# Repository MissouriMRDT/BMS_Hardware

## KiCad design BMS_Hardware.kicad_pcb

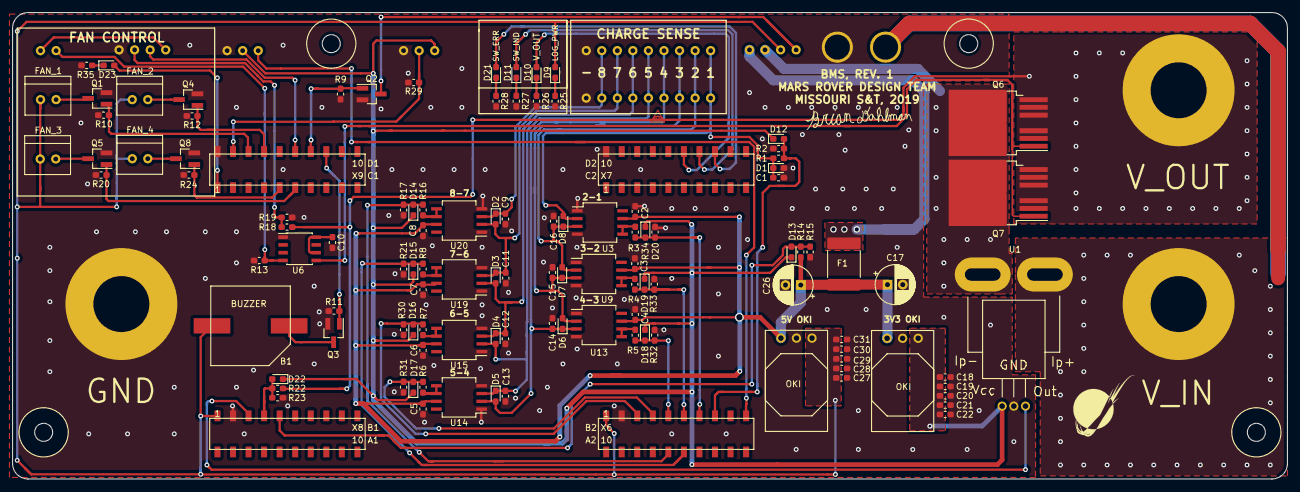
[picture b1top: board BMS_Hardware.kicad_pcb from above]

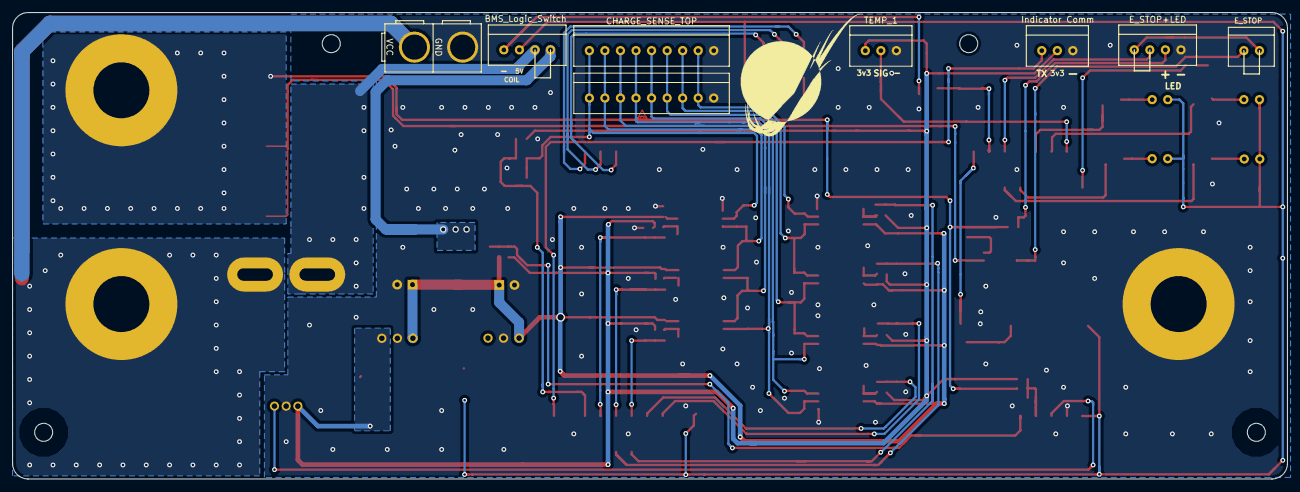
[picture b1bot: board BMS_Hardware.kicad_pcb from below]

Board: 2 copper layers, 208.3 x 76.2 mm, 123 parts (8 on the bottom side), 63 nets.

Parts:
B1: BUZZER_SMI_1324_TW_5V_2_R
C1, C2, C3, C4, C5, C6, C7, C8, C9, C11, C12, C13, C14, C15, C16: 1u; C_0603_1608Metric_Pad1.05x0.95mm_HandSolder
C10, C18, C19, C20, C21, C27, C28, C29, C30: 10u; C_0603_1608Metric_Pad1.05x0.95mm_HandSolder
C17, C26: 22u 50V; CP_Radial_D6.3mm_P2.50mm
C22, C31: 0.1u; C_0603_1608Metric_Pad1.05x0.95mm_HandSolder
Conn1: CHARGE_SENSE_BOTTOM; MOLEX_SL_09_Vertical
Conn2: CHARGE_SENSE_TOP; MOLEX_SL_09_Vertical
Conn3: AndersonPP; Vertical Anderson Double
D1, D2, D3, D4, D5, D6, D7, D8: 7.5V; D_0603_1608Metric_Pad1.05x0.95mm_HandSolder
D9: LOG_PWR_LED; LED_0603_1608Metric_Pad1.05x0.95mm_HandSolder
D10: PACK_V_IND_LED_ORANGE; LED_0603_1608Metric_Pad1.05x0.95mm_HandSolder
D11: SW_IND_LED_BLUE; LED_0603_1608Metric_Pad1.05x0.95mm_HandSolder
D12, D13, D14, D15, D16, D17, D18, D19, D20, D22: D_Schottky; D_0603_1608Metric_Pad1.05x0.95mm_HandSolder
D21: SW_ERR_LED_RED; LED_0603_1608Metric_Pad1.05x0.95mm_HandSolder
D23: FAN_PWR_LED_ORANGE; LED_0603_1608Metric_Pad1.05x0.95mm_HandSolder
F1: PTC2920; Fuse_2920_7451Metric
Q1, Q2, Q3, Q4, Q5, Q8: 2N7002PW; SOT-23_Handsoldering
Q6, Q7: IRLS3034-7P; IRLS3034_TO-263-7_P
R1, R3, R4, R5, R6, R7, R8, R9, R13, R16, R19: 10k; R_0603_1608Metric_Pad1.05x0.95mm_HandSolder
R2, R17, R21, R30, R31, R32, R33, R34: 36.5k; R_0603_1608Metric_Pad1.05x0.95mm_HandSolder
R10, R12, R20, R24: 100K; R_0603_1608Metric_Pad1.05x0.95mm_HandSolder
R11: 10K; R_0603_1608Metric_Pad1.05x0.95mm_HandSolder
R14, R22: 1M; R_0603_1608Metric_Pad1.05x0.95mm_HandSolder
R15, R23: 100k; R_0603_1608Metric_Pad1.05x0.95mm_HandSolder
R18: 4k; R_0603_1608Metric_Pad1.05x0.95mm_HandSolder
R25, R27, R28, R35: 500; R_0603_1608Metric_Pad1.05x0.95mm_HandSolder
R26: 1.5k; R_0603_1608Metric_Pad1.05x0.95mm_HandSolder
R29: 4.7k; R_0603_1608Metric_Pad1.05x0.95mm_HandSolder
U1: ACS759ECB-200B-PFF-T; PFF_Leadform_5pins
U2: FAN_1; MOLEX_SL_02_Vertical
U3, U9, U13, U14, U15, U19, U20: INA132; SO-8_5.3x6.2mm_P1.27mm
U4: FAN_2; MOLEX_SL_02_Vertical
U5: BMS_Logic_Switch; MOLEX_SL_04_Vertical
U6: LT1910; SOIC-8_3.9x4.9mm_Pitch1.27mm
U7: E_STOP; MOLEX_SL_02_Vertical
U8: FAN_3; MOLEX_SL_02_Vertical
U10: E_STOP+LED; MOLEX_SL_04_Vertical
U11: TEMP_1; MOLEX_SL_03_Vertical
U12: FAN_4; MOLEX_SL_02_Vertical
U16, U18: OKI; OKI_Horizontal
U17: Indicator Comm; MOLEX_SL_03_Vertical
U21: TM4C129E_Launchpad; TM4C129E_Launchpad_FULL_Top_SMD
V1, V2, V3: BATT_PWR_VIA

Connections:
+3V3: C18.1, C19.1, C20.1, C21.1, C22.1, D12.1, D13.1, D14.1, D15.1, D16.1, D17.1, D18.1, D19.1, D20.1, D22.1, U1.1, U11.1, U16.3, U17.2
+5V: B1.1, C27.1, C28.1, C29.1, C30.1, C31.1, D9.2, U2.1, U4.1, U5.2, U8.1, U12.1, U18.3, U21.+5V
/V_IN: Conn3.2, U1.4, V2.1
BUZZER: Q3.1, R11.2, U21.PN2
CELL_1: C1.2, Conn1.1, Conn2.1, D1.1, D8.2, R1.2, U3.2
CELL_1-GND_SENSE: D12.2, R1.1, R2.1, U21.PK3
CELL_2: C16.1, Conn1.2, Conn2.2, D7.2, D8.1, U3.3, U9.2
CELL_2-1_SENSE: D20.2, R3.1, R34.1, U21.PK2
CELL_3: C15.1, Conn1.3, Conn2.3, D6.2, D7.1, U9.3, U13.2
CELL_3-2_SENSE: D19.2, R4.1, R33.1, U21.PK1
CELL_4: C14.1, Conn1.4, Conn2.4, D5.2, D6.1, U13.3, U14.2
CELL_4-3_SENSE: D18.2, R5.1, R32.1, U21.PK0
CELL_5: C13.1, Conn1.5, Conn2.5, D4.2, D5.1, U14.3, U15.2
CELL_5-4_SENSE: D17.2, R6.1, R31.1, U21.PB5
CELL_6: C12.1, Conn1.6, Conn2.6, D3.2, D4.1, U15.3, U19.2
CELL_6-5_SENSE: D16.2, R7.1, R30.1, U21.PB4
CELL_7: C11.2, Conn1.7, Conn2.7, D2.2, D3.1, U19.3, U20.2
CELL_7-6_SENSE: D15.2, R8.1, R21.1, U21.PD5
CELL_8: C9.1, Conn1.8, Conn2.8, D2.1, U20.3
CELL_8-7_SENSE: D14.2, R16.1, R17.1, U21.PD4
E-Stop_Gate: Q6.1, Q7.1, U6.5
FAN_CTL_1: Q1.1, R10.2, U21.PH2
FAN_CTL_2: Q4.1, R12.2, U21.PH3
FAN_CTL_3: Q5.1, R20.2, U21.PL5
FAN_CTL_4: Q8.1, R24.2, U21.PL4
FAN_PWR: D23.2, U21.PF1
GND: C1.1, C2.1, C3.1, C4.1, C5.1, C6.1, C7.1, C8.2, C9.2, C10.2, C11.1, C12.2, C13.2, C14.2, C15.2, C16.2, C17.2, C18.2, C19.2, C20.2, C21.2, C22.2, C26.2, C27.2, C28.2, C29.2, C30.2, C31.2, Conn1.9, Conn2.9, Conn3.1, D1.2, Q1.2, Q2.2, Q3.2, Q4.2, Q5.2, Q8.2, R2.2, R9.2, R10.1, R11.1, R12.1, R13.2, R15.2, R17.2, R19.2, R20.1, R21.2, R23.1, R24.1, R25.2, R26.2, R27.2, R28.2, R29.2, R30.2, R31.2, R32.2, R33.2, R34.2, R35.2, U1.2, U3.1, U3.4, U6.1, U9.1, U9.4, U10.4, U11.3, U13.1, U13.4, U14.1, U14.4, U15.1, U15.4, U16.2, U17.3, U18.2, U19.1, U19.4, U20.1, U20.4, U21.GND, V1.1
LOGIC_PWR: C2.2, C3.2, C4.2, C5.2, C6.2, C7.2, C8.1, C17.1, C26.1, F1.1, R14.1, U3.7, U9.7, U13.7, U14.7, U15.7, U16.1, U18.1, U19.7, U20.7
LOGIC_SWITCH: Q2.1, R9.1, U21.PD0
unnamed: B1.2, Q3.3
unnamed: C10.1, U6.6, U6.8
unnamed: D9.1, R25.1
unnamed: D10.1, R26.1
unnamed: D11.1, R27.1
unnamed: D21.1, R28.1
unnamed: D23.1, R35.1
unnamed: F1.2, U5.4
unnamed: Q1.3, U2.2
unnamed: Q2.3, U5.1
unnamed: Q4.3, U4.2
unnamed: Q5.3, U8.2
unnamed: Q6.2, Q7.2, U1.5, U5.3
unnamed: Q8.3, U12.2
unnamed: R3.2, U3.5, U3.6
unnamed: R4.2, U9.5, U9.6
unnamed: R5.2, U13.5, U13.6
unnamed: R6.2, U14.5, U14.6
unnamed: R7.2, U15.5, U15.6
unnamed: R8.2, U19.5, U19.6
unnamed: R13.1, U6.4, U7.1
unnamed: R16.2, U20.5, U20.6
unnamed: R18.1, R19.1, U10.3
unnamed: U7.2, U10.1
PACK_GATE: U10.2, U21.PD1
PACK_I_SENSE: U1.3, U21.PE0
PACK_V_IND: D10.2, U21.PQ2
SER_TX_IND: U17.1, U21.PA5
SW_ERR: D21.2, U21.PP3
SW_IND: D11.2, U21.PQ3
TEMP_D_OUT: R29.1, U11.2, U21.PM3
V_LOG_SENSE: D13.2, R14.2, R15.1, U21.PE2
V_OUT: Q6.3, Q7.3, R18.2, R22.1, V3.1
V_OUT_SENSE: D22.2, R22.2, R23.2, U21.PE1
